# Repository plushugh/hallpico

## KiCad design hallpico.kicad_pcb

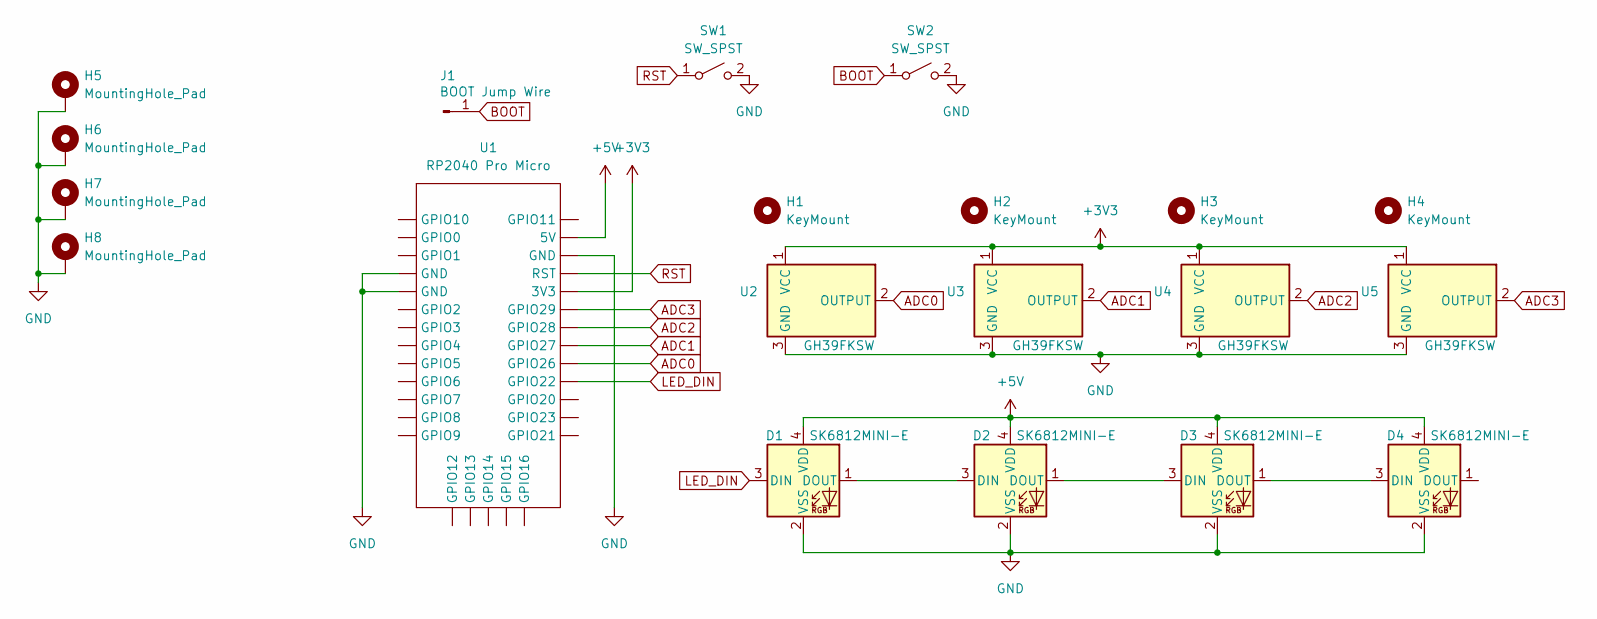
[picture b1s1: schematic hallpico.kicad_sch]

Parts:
D1, D2, D3, D4: SK6812MINI-E; SK6812-MINI-E
H1, H2, H3, H4: KeyMount; SW_HE_MX_PCB
H5, H6, H7, H8: MountingHole_Pad; MountingHole_2.5mm_Pad_Via
J1: BOOT Jump Wire; PinHeader_1x01_P2.54mm_Vertical
SW1, SW2: SW_SPST; SW_SPST_PTS810
U1: RP2040 Pro Micro; RP2040_ProMicro
U2, U3, U4, U5: GH39FKSW; SOT-23; LCSC C266230

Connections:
+3V3: U1.5 (3V3), U2.1 (VCC), U3.1 (VCC), U4.1 (VCC), U5.1 (VCC)
+5V: D1.4 (VDD), D2.4 (VDD), D3.4 (VDD), D4.4 (VDD), U1.2 (5V)
ADC0: U1.9 (GPIO26), U2.2 (OUTPUT)
ADC1: U1.8 (GPIO27), U3.2 (OUTPUT)
ADC2: U1.7 (GPIO28), U4.2 (OUTPUT)
ADC3: U1.6 (GPIO29), U5.2 (OUTPUT)
BOOT: J1.1, SW2.1 (A)
GND: D1.2 (VSS), D2.2 (VSS), D3.2 (VSS), D4.2 (VSS), H5.1, H6.1, H7.1, H8.1, SW1.2 (B), SW2.2 (B), U1.3 (GND), U1.27 (GND), U1.28 (GND), U2.3 (GND), U3.3 (GND), U4.3 (GND), U5.3 (GND)
LED_DIN: D1.3 (DIN), U1.10 (GPIO22)
unnamed: D1.1 (DOUT), D2.3 (DIN)
unnamed: D2.1 (DOUT), D3.3 (DIN)
unnamed: D3.1 (DOUT), D4.3 (DIN)
RST: SW1.1 (A), U1.4 (RST)

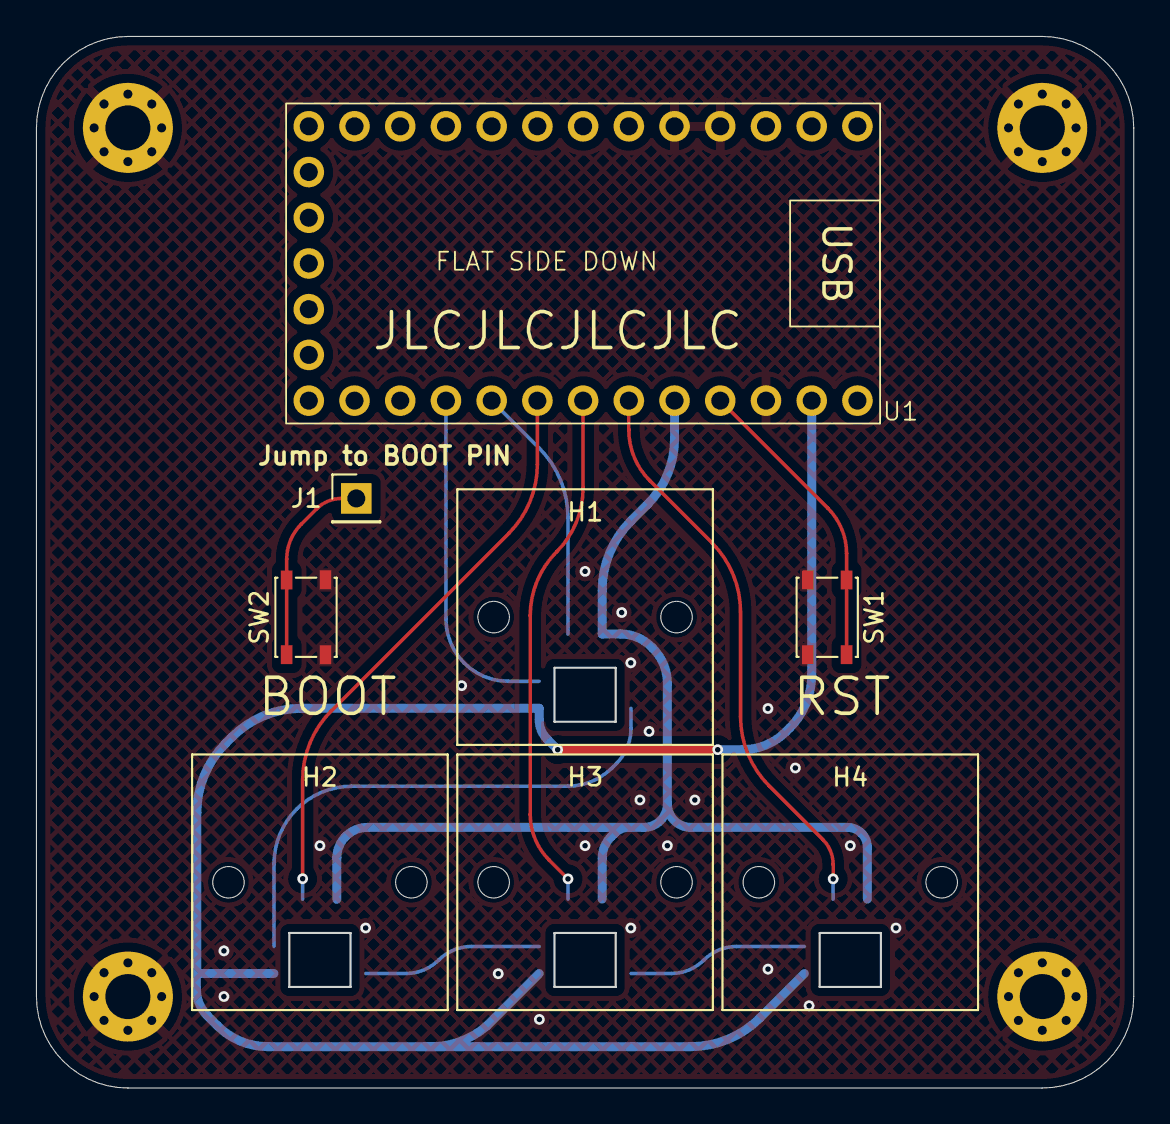
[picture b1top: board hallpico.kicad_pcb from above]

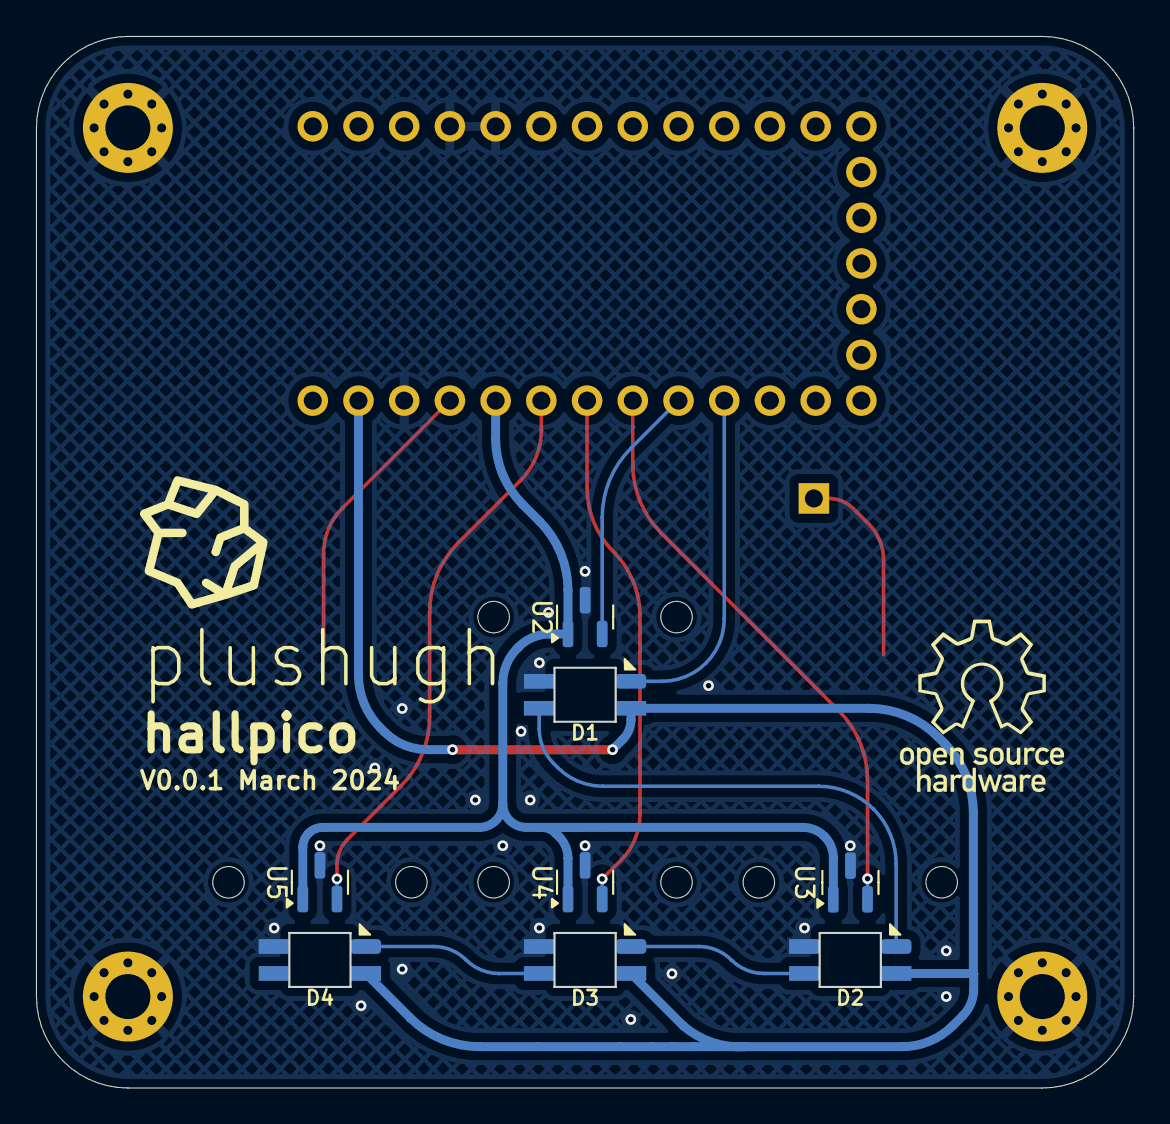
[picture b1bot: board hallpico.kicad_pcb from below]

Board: 2 copper layers, 60.9 x 58.3 mm, 20 parts (8 on the bottom side), 13 nets.

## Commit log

2024-03-03 feat: add initial files
2024-03-03 fix: pro micro not mini pico
2024-03-03 fix: update board with naming fix
2024-03-05 fix: cleanup
